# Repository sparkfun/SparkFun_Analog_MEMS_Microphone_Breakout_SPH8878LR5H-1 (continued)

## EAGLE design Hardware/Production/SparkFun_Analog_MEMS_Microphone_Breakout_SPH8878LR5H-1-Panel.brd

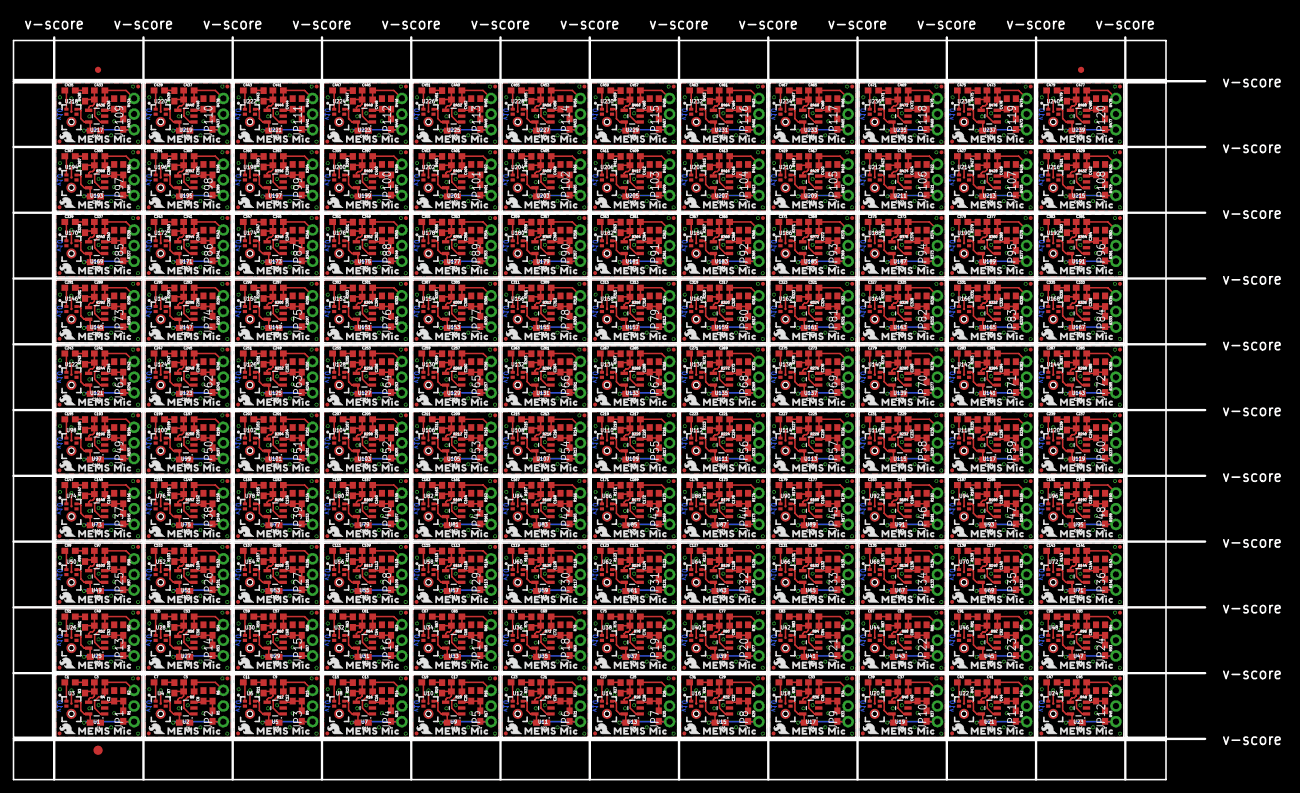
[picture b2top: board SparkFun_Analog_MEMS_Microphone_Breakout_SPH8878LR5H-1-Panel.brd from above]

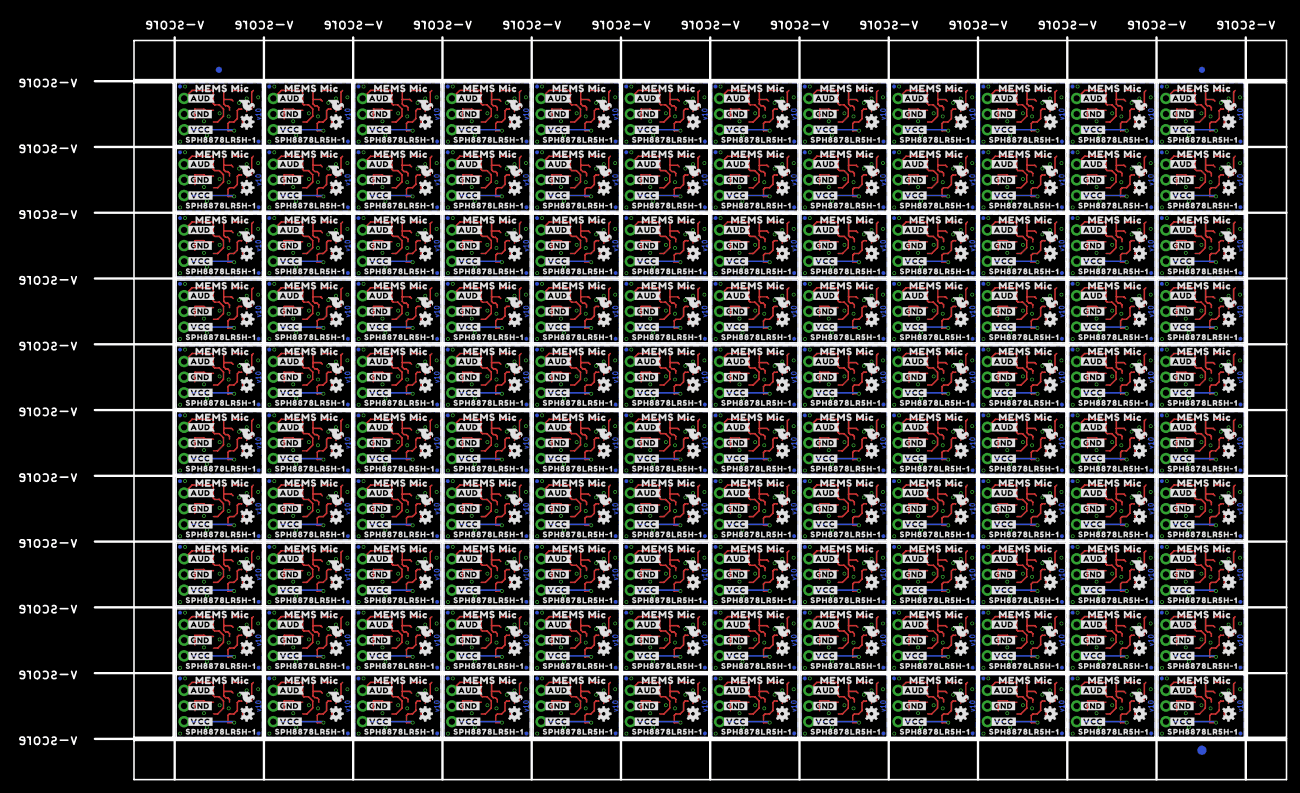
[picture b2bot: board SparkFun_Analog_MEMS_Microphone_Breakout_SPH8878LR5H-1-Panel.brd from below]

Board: 2 copper layers, 193.3 x 120.4 mm, 3006 parts (1203 on the bottom side), 960 nets.

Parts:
C1, C7, C11, C15, C19, C23, C27, C31, C35, C39, C43, C47, C51, C55, C59, C63, C67, C71, C75, C79, C83, C87, C91, C95, C99, C103, C107, C111, C115, C119, C123, C127, C131, C135, C139, C143, C147, C151, C155, C159, C163, C167, C171, C175, C179, C183, C187, C191, C195, C199, C203, C207, C211, C215, C219, C223, C227, C231, C235, C239, C243, C247, C251, C255, C259, C263, C267, C271, C275, C279, C283, C287, C291, C295, C299, C303, C307, C311, C315, C319, C323, C327, C331, C335, C339, C343, C347, C351, C355, C359, C363, C367, C371, C375, C379, C383, C387, C391, C395, C399, C403, C407, C411, C415, C419, C423, C427, C431, C435, C439, C443, C447, C451, C455, C459, C463, C467, C471, C475, C479: 4.7uF; 0603
C2, C8, C12, C16, C20, C24, C28, C32, C36, C40, C44, C48, C52, C56, C60, C64, C68, C72, C76, C80, C84, C88, C92, C96, C100, C104, C108, C112, C116, C120, C124, C128, C132, C136, C140, C144, C148, C152, C156, C160, C164, C168, C172, C176, C180, C184, C188, C192, C196, C200, C204, C208, C212, C216, C220, C224, C228, C232, C236, C240, C244, C248, C252, C256, C260, C264, C268, C272, C276, C280, C284, C288, C292, C296, C300, C304, C308, C312, C316, C320, C324, C328, C332, C336, C340, C344, C348, C352, C356, C360, C364, C368, C372, C376, C380, C384, C388, C392, C396, C400, C404, C408, C412, C416, C420, C424, C428, C432, C436, C440, C444, C448, C452, C456, C460, C464, C468, C472, C476, C480: 1.0uF; 0603
C3, C5, C9, C13, C17, C21, C25, C29, C33, C37, C41, C45, C49, C53, C57, C61, C65, C69, C73, C77, C81, C85, C89, C93, C97, C101, C105, C109, C113, C117, C121, C125, C129, C133, C137, C141, C145, C149, C153, C157, C161, C165, C169, C173, C177, C181, C185, C189, C193, C197, C201, C205, C209, C213, C217, C221, C225, C229, C233, C237, C241, C245, C249, C253, C257, C261, C265, C269, C273, C277, C281, C285, C289, C293, C297, C301, C305, C309, C313, C317, C321, C325, C329, C333, C337, C341, C345, C349, C353, C357, C361, C365, C369, C373, C377, C381, C385, C389, C393, C397, C401, C405, C409, C413, C417, C421, C425, C429, C433, C437, C441, C445, C449, C453, C457, C461, C465, C469, C473, C477: 27pF; 0603
C4, C6, C10, C14, C18, C22, C26, C30, C34, C38, C42, C46, C50, C54, C58, C62, C66, C70, C74, C78, C82, C86, C90, C94, C98, C102, C106, C110, C114, C118, C122, C126, C130, C134, C138, C142, C146, C150, C154, C158, C162, C166, C170, C174, C178, C182, C186, C190, C194, C198, C202, C206, C210, C214, C218, C222, C226, C230, C234, C238, C242, C246, C250, C254, C258, C262, C266, C270, C274, C278, C282, C286, C290, C294, C298, C302, C306, C310, C314, C318, C322, C326, C330, C334, C338, C342, C346, C350, C354, C358, C362, C366, C370, C374, C378, C382, C386, C390, C394, C398, C402, C406, C410, C414, C418, C422, C426, C430, C434, C438, C442, C446, C450, C454, C458, C462, C466, C470, C474, C478: 0.1uF; 0603
E$1, E$2, E$3, E$4: FIDUCIAL-1X2
E$5, E$6: FIDUCIAL-1.5X3
FD1, FD2, FD3, FD4, FD5, FD6, FD7, FD8, FD9, FD10, FD11, FD12, FD13, FD14, FD15, FD16, FD17, FD18, FD19, FD20, FD21, FD22, FD23, FD24, FD25, FD26, FD27, FD28, FD29, FD30, FD31, FD32, FD33, FD34, FD35, FD36, FD37, FD38, FD39, FD40, FD41, FD42, FD43, FD44, FD45, FD46, FD47, FD48, FD49, FD50, FD51, FD52, FD53, FD54, FD55, FD56, FD57, FD58, FD59, FD60, FD61, FD62, FD63, FD64, FD65, FD66, FD67, FD68, FD69, FD70, FD71, FD72, FD73, FD74, FD75, FD76, FD77, FD78, FD79, FD80, FD81, FD82, FD83, FD84, FD85, FD86, FD87, FD88, FD89, FD90, FD91, FD92, FD93, FD94, FD95, FD96, FD97, FD98, FD99, FD100, FD101, FD102, FD103, FD104, FD105, FD106, FD107, FD108, FD109, FD110, FD111, FD112, FD113, FD114, FD115, FD116, FD117, FD118, FD119, FD120, FD121, FD122, FD123, FD124, FD125, FD126, FD127, FD128, FD129, FD130, FD131, FD132, FD133, FD134, FD135, FD136, FD137, FD138, FD139, FD140, FD141, FD142, FD143, FD144, FD145, FD146, FD147, FD148, FD149, FD150, FD151, FD152, FD153, FD154, FD155, FD156, FD157, FD158, FD159, FD160, FD161, FD162, FD163, FD164, FD165, FD166, FD167, FD168, FD169, FD170, FD171, FD172, FD173, FD174, FD175, FD176, FD177, FD178, FD179, FD180, FD181, FD182, FD183, FD184, FD185, FD186, FD187, FD188, FD189, FD190, FD191, FD192, FD193, FD194, FD195, FD196, FD197, FD198, FD199, FD200, FD201, FD202, FD203, FD204, FD205, FD206, FD207, FD208, FD209, FD210, FD211, FD212, FD213, FD214, FD215, FD216, FD217, FD218, FD219, FD220, FD221, FD222, FD223, FD224, FD225, FD226, FD227, FD228, FD229, FD230, FD231, FD232, FD233, FD234, FD235, FD236, FD237, FD238, FD239, FD240, FD241, FD242, FD243, FD244, FD245, FD246, FD247, FD248, FD249, FD250, FD251, FD252, FD253, FD254, FD255, FD256, FD257, FD258, FD259, FD260, FD261, FD262, FD263, FD264, FD265, FD266, FD267, FD268, FD269, FD270, FD271, FD272, FD273, FD274, FD275, FD276, FD277, FD278, FD279, FD280, FD281, FD282, FD283, FD284, FD285, FD286, FD287, FD288, FD289, FD290, FD291, FD292, FD293, FD294, FD295, FD296, FD297, FD298, FD299, FD300, FD301, FD302, FD303, FD304, FD305, FD306, FD307, FD308, FD309, FD310, FD311, FD312, FD313, FD314, FD315, FD316, FD317, FD318, FD319, FD320, FD321, FD322, FD323, FD324, FD325, FD326, FD327, FD328, FD329, FD330, FD331, FD332, FD333, FD334, FD335, FD336, FD337, FD338, FD339, FD340, FD341, FD342, FD343, FD344, FD345, FD346, FD347, FD348, FD349, FD350, FD351, FD352, FD353, FD354, FD355, FD356, FD357, FD358, FD359, FD360, FD361, FD362, FD363, FD364, FD365, FD366, FD367, FD368, FD369, FD370, FD371, FD372, FD373, FD374, FD375, FD376, FD377, FD378, FD379, FD380, FD381, FD382, FD383, FD384, FD385, FD386, FD387, FD388, FD389, FD390, FD391, FD392, FD393, FD394, FD395, FD396, FD397, FD398, FD399, FD400, FD401, FD402, FD403, FD404, FD405, FD406, FD407, FD408, FD409, FD410, FD411, FD412, FD413, FD414, FD415, FD416, FD417, FD418, FD419, FD420, FD421, FD422, FD423, FD424, FD425, FD426, FD427, FD428, FD429, FD430, FD431, FD432, FD433, FD434, FD435, FD436, FD437, FD438, FD439, FD440, FD441, FD442, FD443, FD444, FD445, FD446, FD447, FD448, FD449, FD450, FD451, FD452, FD453, FD454, FD455, FD456, FD457, FD458, FD459, FD460, FD461, FD462, FD463, FD464, FD465, FD466, FD467, FD468, FD469, FD470, FD471, FD472, FD473, FD474, FD475, FD476, FD477, FD478, FD479, FD480: FIDUCIALUFIDUCIAL; FIDUCIAL-MICRO
JP1, JP2, JP3, JP4, JP5, JP6, JP7, JP8, JP9, JP10, JP11, JP12, JP13, JP14, JP15, JP16, JP17, JP18, JP19, JP20, JP21, JP22, JP23, JP24, JP25, JP26, JP27, JP28, JP29, JP30, JP31, JP32, JP33, JP34, JP35, JP36, JP37, JP38, JP39, JP40, JP41, JP42, JP43, JP44, JP45, JP46, JP47, JP48, JP49, JP50, JP51, JP52, JP53, JP54, JP55, JP56, JP57, JP58, JP59, JP60, JP61, JP62, JP63, JP64, JP65, JP66, JP67, JP68, JP69, JP70, JP71, JP72, JP73, JP74, JP75, JP76, JP77, JP78, JP79, JP80, JP81, JP82, JP83, JP84, JP85, JP86, JP87, JP88, JP89, JP90, JP91, JP92, JP93, JP94, JP95, JP96, JP97, JP98, JP99, JP100, JP101, JP102, JP103, JP104, JP105, JP106, JP107, JP108, JP109, JP110, JP111, JP112, JP113, JP114, JP115, JP116, JP117, JP118, JP119, JP120: 1X03_NO_SILK
LOGO1, LOGO3, LOGO4, LOGO6, LOGO7, LOGO9, LOGO10, LOGO12, LOGO13, LOGO15, LOGO16, LOGO18, LOGO19, LOGO21, LOGO22, LOGO24, LOGO25, LOGO27, LOGO28, LOGO30, LOGO31, LOGO33, LOGO34, LOGO36, LOGO37, LOGO39, LOGO40, LOGO42, LOGO43, LOGO45, LOGO46, LOGO48, LOGO49, LOGO51, LOGO52, LOGO54, LOGO55, LOGO57, LOGO58, LOGO60, LOGO61, LOGO63, LOGO64, LOGO66, LOGO67, LOGO69, LOGO70, LOGO72, LOGO73, LOGO75, LOGO76, LOGO78, LOGO79, LOGO81, LOGO82, LOGO84, LOGO85, LOGO87, LOGO88, LOGO90, LOGO91, LOGO93, LOGO94, LOGO96, LOGO97, LOGO99, LOGO100, LOGO102, LOGO103, LOGO105, LOGO106, LOGO108, LOGO109, LOGO111, LOGO112, LOGO114, LOGO115, LOGO117, LOGO118, LOGO120, LOGO121, LOGO123, LOGO124, LOGO126, LOGO127, LOGO129, LOGO130, LOGO132, LOGO133, LOGO135, LOGO136, LOGO138, LOGO139, LOGO141, LOGO142, LOGO144, LOGO145, LOGO147, LOGO148, LOGO150, LOGO151, LOGO153, LOGO154, LOGO156, LOGO157, LOGO159, LOGO160, LOGO162, LOGO163, LOGO165, LOGO166, LOGO168, LOGO169, LOGO171, LOGO172, LOGO174, LOGO175, LOGO177, LOGO178, LOGO180, LOGO181, LOGO183, LOGO184, LOGO186, LOGO187, LOGO189, LOGO190, LOGO192, LOGO193, LOGO195, LOGO196, LOGO198, LOGO199, LOGO201, LOGO202, LOGO204, LOGO205, LOGO207, LOGO208, LOGO210, LOGO211, LOGO213, LOGO214, LOGO216, LOGO217, LOGO219, LOGO220, LOGO222, LOGO223, LOGO225, LOGO226, LOGO228, LOGO229, LOGO231, LOGO232, LOGO234, LOGO235, LOGO237, LOGO238, LOGO240, LOGO241, LOGO243, LOGO244, LOGO246, LOGO247, LOGO249, LOGO250, LOGO252, LOGO253, LOGO255, LOGO256, LOGO258, LOGO259, LOGO261, LOGO262, LOGO264, LOGO265, LOGO267, LOGO268, LOGO270, LOGO271, LOGO273, LOGO274, LOGO276, LOGO277, LOGO279, LOGO280, LOGO282, LOGO283, LOGO285, LOGO286, LOGO288, LOGO289, LOGO291, LOGO292, LOGO294, LOGO295, LOGO297, LOGO298, LOGO300, LOGO301, LOGO303, LOGO304, LOGO306, LOGO307, LOGO309, LOGO310, LOGO312, LOGO313, LOGO315, LOGO316, LOGO318, LOGO319, LOGO321, LOGO322, LOGO324, LOGO325, LOGO327, LOGO328, LOGO330, LOGO331, LOGO333, LOGO334, LOGO336, LOGO337, LOGO339, LOGO340, LOGO342, LOGO343, LOGO345, LOGO346, LOGO348, LOGO349, LOGO351, LOGO352, LOGO354, LOGO355, LOGO357, LOGO358, LOGO360: SFE_LOGO_FLAME.1_INCH; SFE_LOGO_FLAME_.1
LOGO2, LOGO5, LOGO8, LOGO11, LOGO14, LOGO17, LOGO20, LOGO23, LOGO26, LOGO29, LOGO32, LOGO35, LOGO38, LOGO41, LOGO44, LOGO47, LOGO50, LOGO53, LOGO56, LOGO59, LOGO62, LOGO65, LOGO68, LOGO71, LOGO74, LOGO77, LOGO80, LOGO83, LOGO86, LOGO89, LOGO92, LOGO95, LOGO98, LOGO101, LOGO104, LOGO107, LOGO110, LOGO113, LOGO116, LOGO119, LOGO122, LOGO125, LOGO128, LOGO131, LOGO134, LOGO137, LOGO140, LOGO143, LOGO146, LOGO149, LOGO152, LOGO155, LOGO158, LOGO161, LOGO164, LOGO167, LOGO170, LOGO173, LOGO176, LOGO179, LOGO182, LOGO185, LOGO188, LOGO191, LOGO194, LOGO197, LOGO200, LOGO203, LOGO206, LOGO209, LOGO212, LOGO215, LOGO218, LOGO221, LOGO224, LOGO227, LOGO230, LOGO233, LOGO236, LOGO239, LOGO242, LOGO245, LOGO248, LOGO251, LOGO254, LOGO257, LOGO260, LOGO263, LOGO266, LOGO269, LOGO272, LOGO275, LOGO278, LOGO281, LOGO284, LOGO287, LOGO290, LOGO293, LOGO296, LOGO299, LOGO302, LOGO305, LOGO308, LOGO311, LOGO314, LOGO317, LOGO320, LOGO323, LOGO326, LOGO329, LOGO332, LOGO335, LOGO338, LOGO341, LOGO344, LOGO347, LOGO350, LOGO353, LOGO356, LOGO359: OSHW-LOGOMINI; OSHW-LOGO-MINI
OUT-, OUT-1, OUT-2, OUT-3, OUT-4, OUT-5, OUT-6, OUT-7, OUT-8, OUT-9, OUT-10, OUT-11, OUT-12, OUT-13, OUT-14, OUT-15, OUT-16, OUT-17, OUT-18, OUT-19, OUT-20, OUT-21, OUT-22, OUT-23, OUT-24, OUT-25, OUT-26, OUT-27, OUT-28, OUT-29, OUT-30, OUT-31, OUT-32, OUT-33, OUT-34, OUT-35, OUT-36, OUT-37, OUT-38, OUT-39, OUT-40, OUT-41, OUT-42, OUT-43, OUT-44, OUT-45, OUT-46, OUT-47, OUT-48, OUT-49, OUT-50, OUT-51, OUT-52, OUT-53, OUT-54, OUT-55, OUT-56, OUT-57, OUT-58, OUT-59, OUT-60, OUT-61, OUT-62, OUT-63, OUT-64, OUT-65, OUT-66, OUT-67, OUT-68, OUT-69, OUT-70, OUT-71, OUT-72, OUT-73, OUT-74, OUT-75, OUT-76, OUT-77, OUT-78, OUT-79, OUT-80, OUT-81, OUT-82, OUT-83, OUT-84, OUT-85, OUT-86, OUT-87, OUT-88, OUT-89, OUT-90, OUT-91, OUT-92, OUT-93, OUT-94, OUT-95, OUT-96, OUT-97, OUT-98, OUT-99, OUT-100, OUT-101, OUT-102, OUT-103, OUT-104, OUT-105, OUT-106, OUT-107, OUT-108, OUT-109, OUT-110, OUT-111, OUT-112, OUT-113, OUT-114, OUT-115, OUT-116, OUT-117, OUT-118, OUT-119: TP_15TH
R1, R2, R5, R6, R9, R10, R13, R14, R17, R18, R21, R22, R25, R26, R29, R30, R33, R34, R37, R38, R41, R42, R45, R46, R49, R50, R53, R54, R57, R58, R61, R62, R65, R66, R69, R70, R73, R74, R77, R78, R81, R82, R85, R86, R89, R90, R93, R94, R97, R98, R101, R102, R105, R106, R109, R110, R113, R114, R117, R118, R121, R122, R125, R126, R129, R130, R133, R134, R137, R138, R141, R142, R145, R146, R149, R150, R153, R154, R157, R158, R161, R162, R165, R166, R169, R170, R173, R174, R177, R178, R181, R182, R185, R186, R189, R190, R193, R194, R197, R198, R201, R202, R205, R206, R209, R210, R213, R214, R217, R218, R221, R222, R225, R226, R229, R230, R233, R234, R237, R238, R241, R242, R245, R246, R249, R250, R253, R254, R257, R258, R261, R262, R265, R266, R269, R270, R273, R274, R277, R278, R281, R282, R285, R286, R289, R290, R293, R294, R297, R298, R301, R302, R305, R306, R309, R310, R313, R314, R317, R318, R321, R322, R325, R326, R329, R330, R333, R334, R337, R338, R341, R342, R345, R346, R349, R350, R353, R354, R357, R358, R361, R362, R365, R366, R369, R370, R373, R374, R377, R378, R381, R382, R385, R386, R389, R390, R393, R394, R397, R398, R401, R402, R405, R406, R409, R410, R413, R414, R417, R418, R421, R422, R425, R426, R429, R430, R433, R434, R437, R438, R441, R442, R445, R446, R449, R450, R453, R454, R457, R458, R461, R462, R465, R466, R469, R470, R473, R474, R477, R478: 10k; 0603
R3, R7, R11, R15, R19, R23, R27, R31, R35, R39, R43, R47, R51, R55, R59, R63, R67, R71, R75, R79, R83, R87, R91, R95, R99, R103, R107, R111, R115, R119, R123, R127, R131, R135, R139, R143, R147, R151, R155, R159, R163, R167, R171, R175, R179, R183, R187, R191, R195, R199, R203, R207, R211, R215, R219, R223, R227, R231, R235, R239, R243, R247, R251, R255, R259, R263, R267, R271, R275, R279, R283, R287, R291, R295, R299, R303, R307, R311, R315, R319, R323, R327, R331, R335, R339, R343, R347, R351, R355, R359, R363, R367, R371, R375, R379, R383, R387, R391, R395, R399, R403, R407, R411, R415, R419, R423, R427, R431, R435, R439, R443, R447, R451, R455, R459, R463, R467, R471, R475, R479: 4.7k; 0603
R4, R8, R12, R16, R20, R24, R28, R32, R36, R40, R44, R48, R52, R56, R60, R64, R68, R72, R76, R80, R84, R88, R92, R96, R100, R104, R108, R112, R116, R120, R124, R128, R132, R136, R140, R144, R148, R152, R156, R160, R164, R168, R172, R176, R180, R184, R188, R192, R196, R200, R204, R208, R212, R216, R220, R224, R228, R232, R236, R240, R244, R248, R252, R256, R260, R264, R268, R272, R276, R280, R284, R288, R292, R296, R300, R304, R308, R312, R316, R320, R324, R328, R332, R336, R340, R344, R348, R352, R356, R360, R364, R368, R372, R376, R380, R384, R388, R392, R396, R400, R404, R408, R412, R416, R420, R424, R428, R432, R436, R440, R444, R448, R452, R456, R460, R464, R468, R472, R476, R480: 300k; 0603
U1, U2, U5, U7, U9, U11, U13, U15, U17, U19, U21, U23, U25, U27, U29, U31, U33, U35, U37, U39, U41, U43, U45, U47, U49, U51, U53, U55, U57, U59, U61, U63, U65, U67, U69, U71, U73, U75, U77, U79, U81, U83, U85, U87, U89, U91, U93, U95, U97, U99, U101, U103, U105, U107, U109, U111, U113, U115, U117, U119, U121, U123, U125, U127, U129, U131, U133, U135, U137, U139, U141, U143, U145, U147, U149, U151, U153, U155, U157, U159, U161, U163, U165, U167, U169, U171, U173, U175, U177, U179, U181, U183, U185, U187, U189, U191, U193, U195, U197, U199, U201, U203, U205, U207, U209, U211, U213, U215, U217, U219, U221, U223, U225, U227, U229, U231, U233, U235, U237, U239: OPA344; SOT23-5
U3, U4, U6, U8, U10, U12, U14, U16, U18, U20, U22, U24, U26, U28, U30, U32, U34, U36, U38, U40, U42, U44, U46, U48, U50, U52, U54, U56, U58, U60, U62, U64, U66, U68, U70, U72, U74, U76, U78, U80, U82, U84, U86, U88, U90, U92, U94, U96, U98, U100, U102, U104, U106, U108, U110, U112, U114, U116, U118, U120, U122, U124, U126, U128, U130, U132, U134, U136, U138, U140, U142, U144, U146, U148, U150, U152, U154, U156, U158, U160, U162, U164, U166, U168, U170, U172, U174, U176, U178, U180, U182, U184, U186, U188, U190, U192, U194, U196, U198, U200, U202, U204, U206, U208, U210, U212, U214, U216, U218, U220, U222, U224, U226, U228, U230, U232, U234, U236, U238, U240: SPH8878LR5H-1
U$1, U$2, U$7, U$11, U$13, U$17, U$19, U$23, U$25, U$29, U$31, U$35, U$37, U$41, U$43, U$47, U$49, U$53, U$55, U$59, U$61, U$65, U$67, U$71, U$73, U$77, U$79, U$83, U$85, U$89, U$91, U$95, U$97, U$101, U$103, U$107, U$109, U$113, U$115, U$119, U$121, U$125, U$127, U$131, U$133, U$137, U$139, U$143, U$145, U$149, U$151, U$155, U$157, U$161, U$163, U$167, U$169, U$173, U$175, U$179, U$181, U$185, U$187, U$191, U$193, U$197, U$199, U$203, U$205, U$209, U$211, U$215, U$217, U$221, U$223, U$227, U$229, U$233, U$235, U$239, U$241, U$245, U$247, U$251, U$253, U$257, U$259, U$263, U$265, U$269, U$271, U$275, U$277, U$281, U$283, U$287, U$289, U$293, U$295, U$299, U$301, U$305, U$307, U$311, U$313, U$317, U$319, U$323, U$325, U$329, U$331, U$335, U$337, U$341, U$343, U$347, U$349, U$353, U$355, U$359, U$361, U$365, U$367, U$371, U$373, U$377, U$379, U$383, U$385, U$389, U$391, U$395, U$397, U$401, U$403, U$407, U$409, U$413, U$415, U$419, U$421, U$425, U$427, U$431, U$433, U$437, U$439, U$443, U$445, U$449, U$451, U$455, U$457, U$461, U$463, U$467, U$469, U$473, U$475, U$479, U$481, U$485, U$487, U$491, U$493, U$497, U$499, U$503, U$505, U$509, U$511, U$515, U$517, U$521, U$523, U$527, U$529, U$533, U$535, U$539, U$541, U$545, U$547, U$551, U$553, U$557, U$559, U$563, U$565, U$569, U$571, U$575, U$577, U$581, U$583, U$587, U$589, U$593, U$595, U$599, U$601, U$605, U$607, U$611, U$613, U$617, U$619, U$623, U$625, U$629, U$631, U$635, U$637, U$641, U$643, U$647, U$649, U$653, U$655, U$659, U$661, U$665, U$667, U$671, U$673, U$677, U$679, U$683, U$685, U$689, U$691, U$695, U$697, U$701, U$703, U$707, U$709, U$713, U$715, U$719: MEMS_MIC0
U$3, U$6, U$14, U$20, U$26, U$32, U$38, U$44, U$50, U$56, U$62, U$68, U$74, U$80, U$86, U$92, U$98, U$104, U$110, U$116, U$122, U$128, U$134, U$140, U$146, U$152, U$158, U$164, U$170, U$176, U$182, U$188, U$194, U$200, U$206, U$212, U$218, U$224, U$230, U$236, U$242, U$248, U$254, U$260, U$266, U$272, U$278, U$284, U$290, U$296, U$302, U$308, U$314, U$320, U$326, U$332, U$338, U$344, U$350, U$356, U$362, U$368, U$374, U$380, U$386, U$392, U$398, U$404, U$410, U$416, U$422, U$428, U$434, U$440, U$446, U$452, U$458, U$464, U$470, U$476, U$482, U$488, U$494, U$500, U$506, U$512, U$518, U$524, U$530, U$536, U$542, U$548, U$554, U$560, U$566, U$572, U$578, U$584, U$590, U$596, U$602, U$608, U$614, U$620, U$626, U$632, U$638, U$644, U$650, U$656, U$662, U$668, U$674, U$680, U$686, U$692, U$698, U$704, U$710, U$716: #GND#0
U$4, U$8, U$15, U$21, U$27, U$33, U$39, U$45, U$51, U$57, U$63, U$69, U$75, U$81, U$87, U$93, U$99, U$105, U$111, U$117, U$123, U$129, U$135, U$141, U$147, U$153, U$159, U$165, U$171, U$177, U$183, U$189, U$195, U$201, U$207, U$213, U$219, U$225, U$231, U$237, U$243, U$249, U$255, U$261, U$267, U$273, U$279, U$285, U$291, U$297, U$303, U$309, U$315, U$321, U$327, U$333, U$339, U$345, U$351, U$357, U$363, U$369, U$375, U$381, U$387, U$393, U$399, U$405, U$411, U$417, U$423, U$429, U$435, U$441, U$447, U$453, U$459, U$465, U$471, U$477, U$483, U$489, U$495, U$501, U$507, U$513, U$519, U$525, U$531, U$537, U$543, U$549, U$555, U$561, U$567, U$573, U$579, U$585, U$591, U$597, U$603, U$609, U$615, U$621, U$627, U$633, U$639, U$645, U$651, U$657, U$663, U$669, U$675, U$681, U$687, U$693, U$699, U$705, U$711, U$717: #VCC#0
U$5, U$10, U$16, U$22, U$28, U$34, U$40, U$46, U$52, U$58, U$64, U$70, U$76, U$82, U$88, U$94, U$100, U$106, U$112, U$118, U$124, U$130, U$136, U$142, U$148, U$154, U$160, U$166, U$172, U$178, U$184, U$190, U$196, U$202, U$208, U$214, U$220, U$226, U$232, U$238, U$244, U$250, U$256, U$262, U$268, U$274, U$280, U$286, U$292, U$298, U$304, U$310, U$316, U$322, U$328, U$334, U$340, U$346, U$352, U$358, U$364, U$370, U$376, U$382, U$388, U$394, U$400, U$406, U$412, U$418, U$424, U$430, U$436, U$442, U$448, U$454, U$460, U$466, U$472, U$478, U$484, U$490, U$496, U$502, U$508, U$514, U$520, U$526, U$532, U$538, U$544, U$550, U$556, U$562, U$568, U$574, U$580, U$586, U$592, U$598, U$604, U$610, U$616, U$622, U$628, U$634, U$640, U$646, U$652, U$658, U$664, U$670, U$676, U$682, U$688, U$694, U$700, U$706, U$712, U$718: #AUD#0
U$9, U$12, U$18, U$24, U$30, U$36, U$42, U$48, U$54, U$60, U$66, U$72, U$78, U$84, U$90, U$96, U$102, U$108, U$114, U$120, U$126, U$132, U$138, U$144, U$150, U$156, U$162, U$168, U$174, U$180, U$186, U$192, U$198, U$204, U$210, U$216, U$222, U$228, U$234, U$240, U$246, U$252, U$258, U$264, U$270, U$276, U$282, U$288, U$294, U$300, U$306, U$312, U$318, U$324, U$330, U$336, U$342, U$348, U$354, U$360, U$366, U$372, U$378, U$384, U$390, U$396, U$402, U$408, U$414, U$420, U$426, U$432, U$438, U$444, U$450, U$456, U$462, U$468, U$474, U$480, U$486, U$492, U$498, U$504, U$510, U$516, U$522, U$528, U$534, U$540, U$546, U$552, U$558, U$564, U$570, U$576, U$582, U$588, U$594, U$600, U$606, U$612, U$618, U$624, U$630, U$636, U$642, U$648, U$654, U$660, U$666, U$672, U$678, U$684, U$690, U$696, U$702, U$708, U$714, U$720: SPH8878LR5H#10

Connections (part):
AUD: C3.2, JP1.3, R4.1, U1.1
AUD1: C5.2, JP2.3, R8.1, U2.1
AUD2: C9.2, JP3.3, R12.1, U5.1
AUD3: C13.2, JP4.3, R16.1, U7.1
AUD4: C17.2, JP5.3, R20.1, U9.1
AUD5: C21.2, JP6.3, R24.1, U11.1
AUD6: C25.2, JP7.3, R28.1, U13.1
AUD7: C29.2, JP8.3, R32.1, U15.1
AUD8: C33.2, JP9.3, R36.1, U17.1
AUD9: C37.2, JP10.3, R40.1, U19.1
AUD10: C41.2, JP11.3, R44.1, U21.1
AUD11: C45.2, JP12.3, R48.1, U23.1
AUD12: C49.2, JP13.3, R52.1, U25.1
AUD13: C53.2, JP14.3, R56.1, U27.1
AUD14: C57.2, JP15.3, R60.1, U29.1
AUD15: C61.2, JP16.3, R64.1, U31.1
AUD16: C65.2, JP17.3, R68.1, U33.1
AUD17: C69.2, JP18.3, R72.1, U35.1
AUD18: C73.2, JP19.3, R76.1, U37.1
AUD19: C77.2, JP20.3, R80.1, U39.1
AUD20: C81.2, JP21.3, R84.1, U41.1
AUD21: C85.2, JP22.3, R88.1, U43.1
AUD22: C89.2, JP23.3, R92.1, U45.1
AUD23: C93.2, JP24.3, R96.1, U47.1
AUD24: C97.2, JP25.3, R100.1, U49.1
AUD25: C101.2, JP26.3, R104.1, U51.1
AUD26: C105.2, JP27.3, R108.1, U53.1
AUD27: C109.2, JP28.3, R112.1, U55.1
AUD28: C113.2, JP29.3, R116.1, U57.1
AUD29: C117.2, JP30.3, R120.1, U59.1
AUD30: C121.2, JP31.3, R124.1, U61.1
AUD31: C125.2, JP32.3, R128.1, U63.1
AUD32: C129.2, JP33.3, R132.1, U65.1
AUD33: C133.2, JP34.3, R136.1, U67.1
AUD34: C137.2, JP35.3, R140.1, U69.1
AUD35: C141.2, JP36.3, R144.1, U71.1
AUD36: C145.2, JP37.3, R148.1, U73.1
AUD37: C149.2, JP38.3, R152.1, U75.1
AUD38: C153.2, JP39.3, R156.1, U77.1
AUD39: C157.2, JP40.3, R160.1, U79.1
AUD40: C161.2, JP41.3, R164.1, U81.1
AUD41: C165.2, JP42.3, R168.1, U83.1
AUD42: C169.2, JP43.3, R172.1, U85.1
AUD43: C173.2, JP44.3, R176.1, U87.1
AUD44: C177.2, JP45.3, R180.1, U89.1
AUD45: C181.2, JP46.3, R184.1, U91.1
AUD46: C185.2, JP47.3, R188.1, U93.1
AUD47: C189.2, JP48.3, R192.1, U95.1
AUD48: C193.2, JP49.3, R196.1, U97.1
AUD49: C197.2, JP50.3, R200.1, U99.1
AUD50: C201.2, JP51.3, R204.1, U101.1
AUD51: C205.2, JP52.3, R208.1, U103.1
AUD52: C209.2, JP53.3, R212.1, U105.1
AUD53: C213.2, JP54.3, R216.1, U107.1
AUD54: C217.2, JP55.3, R220.1, U109.1
AUD55: C221.2, JP56.3, R224.1, U111.1
AUD56: C225.2, JP57.3, R228.1, U113.1
AUD57: C229.2, JP58.3, R232.1, U115.1
AUD58: C233.2, JP59.3, R236.1, U117.1
AUD59: C237.2, JP60.3, R240.1, U119.1
AUD60: C241.2, JP61.3, R244.1, U121.1
AUD61: C245.2, JP62.3, R248.1, U123.1
AUD62: C249.2, JP63.3, R252.1, U125.1
AUD63: C253.2, JP64.3, R256.1, U127.1
AUD64: C257.2, JP65.3, R260.1, U129.1
AUD65: C261.2, JP66.3, R264.1, U131.1
AUD66: C265.2, JP67.3, R268.1, U133.1
AUD67: C269.2, JP68.3, R272.1, U135.1
AUD68: C273.2, JP69.3, R276.1, U137.1
AUD69: C277.2, JP70.3, R280.1, U139.1
AUD70: C281.2, JP71.3, R284.1, U141.1
AUD71: C285.2, JP72.3, R288.1, U143.1
AUD72: C289.2, JP73.3, R292.1, U145.1
AUD73: C293.2, JP74.3, R296.1, U147.1
AUD74: C297.2, JP75.3, R300.1, U149.1
AUD75: C301.2, JP76.3, R304.1, U151.1
AUD76: C305.2, JP77.3, R308.1, U153.1
AUD77: C309.2, JP78.3, R312.1, U155.1
AUD78: C313.2, JP79.3, R316.1, U157.1
AUD79: C317.2, JP80.3, R320.1, U159.1
AUD80: C321.2, JP81.3, R324.1, U161.1
AUD81: C325.2, JP82.3, R328.1, U163.1
AUD82: C329.2, JP83.3, R332.1, U165.1
AUD83: C333.2, JP84.3, R336.1, U167.1
AUD84: C337.2, JP85.3, R340.1, U169.1
AUD85: C341.2, JP86.3, R344.1, U171.1
AUD86: C345.2, JP87.3, R348.1, U173.1
AUD87: C349.2, JP88.3, R352.1, U175.1
AUD88: C353.2, JP89.3, R356.1, U177.1
AUD89: C357.2, JP90.3, R360.1, U179.1
AUD90: C361.2, JP91.3, R364.1, U181.1
AUD91: C365.2, JP92.3, R368.1, U183.1
AUD92: C369.2, JP93.3, R372.1, U185.1
AUD93: C373.2, JP94.3, R376.1, U187.1
AUD94: C377.2, JP95.3, R380.1, U189.1
AUD95: C381.2, JP96.3, R384.1, U191.1
AUD96: C385.2, JP97.3, R388.1, U193.1
AUD97: C389.2, JP98.3, R392.1, U195.1
AUD98: C393.2, JP99.3, R396.1, U197.1
AUD99: C397.2, JP100.3, R400.1, U199.1
AUD100: C401.2, JP101.3, R404.1, U201.1
AUD101: C405.2, JP102.3, R408.1, U203.1
AUD102: C409.2, JP103.3, R412.1, U205.1
AUD103: C413.2, JP104.3, R416.1, U207.1
AUD104: C417.2, JP105.3, R420.1, U209.1
AUD105: C421.2, JP106.3, R424.1, U211.1
AUD106: C425.2, JP107.3, R428.1, U213.1
AUD107: C429.2, JP108.3, R432.1, U215.1
AUD108: C433.2, JP109.3, R436.1, U217.1
AUD109: C437.2, JP110.3, R440.1, U219.1
AUD110: C441.2, JP111.3, R444.1, U221.1
AUD111: C445.2, JP112.3, R448.1, U223.1
AUD112: C449.2, JP113.3, R452.1, U225.1
AUD113: C453.2, JP114.3, R456.1, U227.1
AUD114: C457.2, JP115.3, R460.1, U229.1
AUD115: C461.2, JP116.3, R464.1, U231.1
AUD116: C465.2, JP117.3, R468.1, U233.1
AUD117: C469.2, JP118.3, R472.1, U235.1
AUD118: C473.2, JP119.3, R476.1, U237.1
AUD119: C477.2, JP120.3, R480.1, U239.1
GND: C2.2, C4.1, JP1.2, R2.1, U1.2, U3.2, U3.3, U3.4
GND1: C6.1, C8.2, JP2.2, R6.1, U2.2, U4.2, U4.3, U4.4
GND2: C10.1, C12.2, JP3.2, R10.1, U5.2, U6.2, U6.3, U6.4
GND3: C14.1, C16.2, JP4.2, R14.1, U7.2, U8.2, U8.3, U8.4
GND4: C18.1, C20.2, JP5.2, R18.1, U9.2, U10.2, U10.3, U10.4
GND5: C22.1, C24.2, JP6.2, R22.1, U11.2, U12.2, U12.3, U12.4
GND6: C26.1, C28.2, JP7.2, R26.1, U13.2, U14.2, U14.3, U14.4
GND7: C30.1, C32.2, JP8.2, R30.1, U15.2, U16.2, U16.3, U16.4
GND8: C34.1, C36.2, JP9.2, R34.1, U17.2, U18.2, U18.3, U18.4
GND9: C38.1, C40.2, JP10.2, R38.1, U19.2, U20.2, U20.3, U20.4
GND10: C42.1, C44.2, JP11.2, R42.1, U21.2, U22.2, U22.3, U22.4
GND11: C46.1, C48.2, JP12.2, R46.1, U23.2, U24.2, U24.3, U24.4
GND12: C50.1, C52.2, JP13.2, R50.1, U25.2, U26.2, U26.3, U26.4
GND13: C54.1, C56.2, JP14.2, R54.1, U27.2, U28.2, U28.3, U28.4
GND14: C58.1, C60.2, JP15.2, R58.1, U29.2, U30.2, U30.3, U30.4
GND15: C62.1, C64.2, JP16.2, R62.1, U31.2, U32.2, U32.3, U32.4
GND16: C66.1, C68.2, JP17.2, R66.1, U33.2, U34.2, U34.3, U34.4
GND17: C70.1, C72.2, JP18.2, R70.1, U35.2, U36.2, U36.3, U36.4
GND18: C74.1, C76.2, JP19.2, R74.1, U37.2, U38.2, U38.3, U38.4
GND19: C78.1, C80.2, JP20.2, R78.1, U39.2, U40.2, U40.3, U40.4
GND20: C82.1, C84.2, JP21.2, R82.1, U41.2, U42.2, U42.3, U42.4
GND21: C86.1, C88.2, JP22.2, R86.1, U43.2, U44.2, U44.3, U44.4
GND22: C90.1, C92.2, JP23.2, R90.1, U45.2, U46.2, U46.3, U46.4
GND23: C94.1, C96.2, JP24.2, R94.1, U47.2, U48.2, U48.3, U48.4
GND24: C98.1, C100.2, JP25.2, R98.1, U49.2, U50.2, U50.3, U50.4
GND25: C102.1, C104.2, JP26.2, R102.1, U51.2, U52.2, U52.3, U52.4
GND26: C106.1, C108.2, JP27.2, R106.1, U53.2, U54.2, U54.3, U54.4
GND27: C110.1, C112.2, JP28.2, R110.1, U55.2, U56.2, U56.3, U56.4
GND28: C114.1, C116.2, JP29.2, R114.1, U57.2, U58.2, U58.3, U58.4
GND29: C118.1, C120.2, JP30.2, R118.1, U59.2, U60.2, U60.3, U60.4
GND30: C122.1, C124.2, JP31.2, R122.1, U61.2, U62.2, U62.3, U62.4
GND31: C126.1, C128.2, JP32.2, R126.1, U63.2, U64.2, U64.3, U64.4
GND32: C130.1, C132.2, JP33.2, R130.1, U65.2, U66.2, U66.3, U66.4
GND33: C134.1, C136.2, JP34.2, R134.1, U67.2, U68.2, U68.3, U68.4
GND34: C138.1, C140.2, JP35.2, R138.1, U69.2, U70.2, U70.3, U70.4
GND35: C142.1, C144.2, JP36.2, R142.1, U71.2, U72.2, U72.3, U72.4
GND36: C146.1, C148.2, JP37.2, R146.1, U73.2, U74.2, U74.3, U74.4
GND37: C150.1, C152.2, JP38.2, R150.1, U75.2, U76.2, U76.3, U76.4
GND38: C154.1, C156.2, JP39.2, R154.1, U77.2, U78.2, U78.3, U78.4
GND39: C158.1, C160.2, JP40.2, R158.1, U79.2, U80.2, U80.3, U80.4
GND40: C162.1, C164.2, JP41.2, R162.1, U81.2, U82.2, U82.3, U82.4
GND41: C166.1, C168.2, JP42.2, R166.1, U83.2, U84.2, U84.3, U84.4
GND42: C170.1, C172.2, JP43.2, R170.1, U85.2, U86.2, U86.3, U86.4
GND43: C174.1, C176.2, JP44.2, R174.1, U87.2, U88.2, U88.3, U88.4
GND44: C178.1, C180.2, JP45.2, R178.1, U89.2, U90.2, U90.3, U90.4
GND45: C182.1, C184.2, JP46.2, R182.1, U91.2, U92.2, U92.3, U92.4
GND46: C186.1, C188.2, JP47.2, R186.1, U93.2, U94.2, U94.3, U94.4
GND47: C190.1, C192.2, JP48.2, R190.1, U95.2, U96.2, U96.3, U96.4
GND48: C194.1, C196.2, JP49.2, R194.1, U97.2, U98.2, U98.3, U98.4
GND49: C198.1, C200.2, JP50.2, R198.1, U99.2, U100.2, U100.3, U100.4
GND50: C202.1, C204.2, JP51.2, R202.1, U101.2, U102.2, U102.3, U102.4
GND51: C206.1, C208.2, JP52.2, R206.1, U103.2, U104.2, U104.3, U104.4
GND52: C210.1, C212.2, JP53.2, R210.1, U105.2, U106.2, U106.3, U106.4
GND53: C214.1, C216.2, JP54.2, R214.1, U107.2, U108.2, U108.3, U108.4
GND54: C218.1, C220.2, JP55.2, R218.1, U109.2, U110.2, U110.3, U110.4
GND55: C222.1, C224.2, JP56.2, R222.1, U111.2, U112.2, U112.3, U112.4
GND56: C226.1, C228.2, JP57.2, R226.1, U113.2, U114.2, U114.3, U114.4
GND57: C230.1, C232.2, JP58.2, R230.1, U115.2, U116.2, U116.3, U116.4
GND58: C234.1, C236.2, JP59.2, R234.1, U117.2, U118.2, U118.3, U118.4
GND59: C238.1, C240.2, JP60.2, R238.1, U119.2, U120.2, U120.3, U120.4
GND60: C242.1, C244.2, JP61.2, R242.1, U121.2, U122.2, U122.3, U122.4
GND61: C246.1, C248.2, JP62.2, R246.1, U123.2, U124.2, U124.3, U124.4
GND62: C250.1, C252.2, JP63.2, R250.1, U125.2, U126.2, U126.3, U126.4
GND63: C254.1, C256.2, JP64.2, R254.1, U127.2, U128.2, U128.3, U128.4
GND64: C258.1, C260.2, JP65.2, R258.1, U129.2, U130.2, U130.3, U130.4
GND65: C262.1, C264.2, JP66.2, R262.1, U131.2, U132.2, U132.3, U132.4
GND66: C266.1, C268.2, JP67.2, R266.1, U133.2, U134.2, U134.3, U134.4
GND67: C270.1, C272.2, JP68.2, R270.1, U135.2, U136.2, U136.3, U136.4
GND68: C274.1, C276.2, JP69.2, R274.1, U137.2, U138.2, U138.3, U138.4
GND69: C278.1, C280.2, JP70.2, R278.1, U139.2, U140.2, U140.3, U140.4
GND70: C282.1, C284.2, JP71.2, R282.1, U141.2, U142.2, U142.3, U142.4
GND71: C286.1, C288.2, JP72.2, R286.1, U143.2, U144.2, U144.3, U144.4
GND72: C290.1, C292.2, JP73.2, R290.1, U145.2, U146.2, U146.3, U146.4
GND73: C294.1, C296.2, JP74.2, R294.1, U147.2, U148.2, U148.3, U148.4
GND74: C298.1, C300.2, JP75.2, R298.1, U149.2, U150.2, U150.3, U150.4
GND75: C302.1, C304.2, JP76.2, R302.1, U151.2, U152.2, U152.3, U152.4
GND76: C306.1, C308.2, JP77.2, R306.1, U153.2, U154.2, U154.3, U154.4
GND77: C310.1, C312.2, JP78.2, R310.1, U155.2, U156.2, U156.3, U156.4
GND78: C314.1, C316.2, JP79.2, R314.1, U157.2, U158.2, U158.3, U158.4
GND79: C318.1, C320.2, JP80.2, R318.1, U159.2, U160.2, U160.3, U160.4
GND80: C322.1, C324.2, JP81.2, R322.1, U161.2, U162.2, U162.3, U162.4
GND81: C326.1, C328.2, JP82.2, R326.1, U163.2, U164.2, U164.3, U164.4
GND82: C330.1, C332.2, JP83.2, R330.1, U165.2, U166.2, U166.3, U166.4
GND83: C334.1, C336.2, JP84.2, R334.1, U167.2, U168.2, U168.3, U168.4
GND84: C338.1, C340.2, JP85.2, R338.1, U169.2, U170.2, U170.3, U170.4
GND85: C342.1, C344.2, JP86.2, R342.1, U171.2, U172.2, U172.3, U172.4
GND86: C346.1, C348.2, JP87.2, R346.1, U173.2, U174.2, U174.3, U174.4
GND87: C350.1, C352.2, JP88.2, R350.1, U175.2, U176.2, U176.3, U176.4
GND88: C354.1, C356.2, JP89.2, R354.1, U177.2, U178.2, U178.3, U178.4
GND89: C358.1, C360.2, JP90.2, R358.1, U179.2, U180.2, U180.3, U180.4
GND90: C362.1, C364.2, JP91.2, R362.1, U181.2, U182.2, U182.3, U182.4
GND91: C366.1, C368.2, JP92.2, R366.1, U183.2, U184.2, U184.3, U184.4
GND92: C370.1, C372.2, JP93.2, R370.1, U185.2, U186.2, U186.3, U186.4
GND93: C374.1, C376.2, JP94.2, R374.1, U187.2, U188.2, U188.3, U188.4
GND94: C378.1, C380.2, JP95.2, R378.1, U189.2, U190.2, U190.3, U190.4
GND95: C382.1, C384.2, JP96.2, R382.1, U191.2, U192.2, U192.3, U192.4
GND96: C386.1, C388.2, JP97.2, R386.1, U193.2, U194.2, U194.3, U194.4
GND97: C390.1, C392.2, JP98.2, R390.1, U195.2, U196.2, U196.3, U196.4
GND98: C394.1, C396.2, JP99.2, R394.1, U197.2, U198.2, U198.3, U198.4
GND99: C398.1, C400.2, JP100.2, R398.1, U199.2, U200.2, U200.3, U200.4
GND100: C402.1, C404.2, JP101.2, R402.1, U201.2, U202.2, U202.3, U202.4
GND101: C406.1, C408.2, JP102.2, R406.1, U203.2, U204.2, U204.3, U204.4
GND102: C410.1, C412.2, JP103.2, R410.1, U205.2, U206.2, U206.3, U206.4
GND103: C414.1, C416.2, JP104.2, R414.1, U207.2, U208.2, U208.3, U208.4
GND104: C418.1, C420.2, JP105.2, R418.1, U209.2, U210.2, U210.3, U210.4
GND105: C422.1, C424.2, JP106.2, R422.1, U211.2, U212.2, U212.3, U212.4
GND106: C426.1, C428.2, JP107.2, R426.1, U213.2, U214.2, U214.3, U214.4
GND107: C430.1, C432.2, JP108.2, R430.1, U215.2, U216.2, U216.3, U216.4
GND108: C434.1, C436.2, JP109.2, R434.1, U217.2, U218.2, U218.3, U218.4
GND109: C438.1, C440.2, JP110.2, R438.1, U219.2, U220.2, U220.3, U220.4
GND110: C442.1, C444.2, JP111.2, R442.1, U221.2, U222.2, U222.3, U222.4
GND111: C446.1, C448.2, JP112.2, R446.1, U223.2, U224.2, U224.3, U224.4
GND112: C450.1, C452.2, JP113.2, R450.1, U225.2, U226.2, U226.3, U226.4
GND113: C454.1, C456.2, JP114.2, R454.1, U227.2, U228.2, U228.3, U228.4
GND114: C458.1, C460.2, JP115.2, R458.1, U229.2, U230.2, U230.3, U230.4
GND115: C462.1, C464.2, JP116.2, R462.1, U231.2, U232.2, U232.3, U232.4
GND116: C466.1, C468.2, JP117.2, R466.1, U233.2, U234.2, U234.3, U234.4
GND117: C470.1, C472.2, JP118.2, R470.1, U235.2, U236.2, U236.3, U236.4
GND118: C474.1, C476.2, JP119.2, R474.1, U237.2, U238.2, U238.3, U238.4
GND119: C478.1, C480.2, JP120.2, R478.1, U239.2, U240.2, U240.3, U240.4
unnamed: C1.1, U3.1
unnamed: C3.1, R3.1, R4.2, U1.4
unnamed: OUT-.1, U3.6
unnamed: C7.1, U4.1
unnamed: C5.1, R7.1, R8.2, U2.4
unnamed: C1.2, R3.2
unnamed: C2.1, R1.1, R2.2, U1.3
unnamed: C7.2, R7.2
unnamed: C8.1, R5.1, R6.2, U2.3
unnamed: OUT-1.1, U4.6
unnamed: C11.1, U6.1
unnamed: C9.1, R11.1, R12.2, U5.4
unnamed: C11.2, R11.2
unnamed: C12.1, R9.1, R10.2, U5.3
unnamed: OUT-2.1, U6.6
unnamed: C15.1, U8.1
unnamed: C13.1, R15.1, R16.2, U7.4
unnamed: C15.2, R15.2
unnamed: C16.1, R13.1, R14.2, U7.3
unnamed: OUT-3.1, U8.6
unnamed: C19.1, U10.1
unnamed: C17.1, R19.1, R20.2, U9.4
unnamed: C19.2, R19.2
unnamed: C20.1, R17.1, R18.2, U9.3
unnamed: OUT-4.1, U10.6
unnamed: C23.1, U12.1
unnamed: C21.1, R23.1, R24.2, U11.4
unnamed: C23.2, R23.2
unnamed: C24.1, R21.1, R22.2, U11.3
unnamed: OUT-5.1, U12.6
unnamed: C27.1, U14.1
unnamed: C25.1, R27.1, R28.2, U13.4
unnamed: C27.2, R27.2
unnamed: C28.1, R25.1, R26.2, U13.3
unnamed: OUT-6.1, U14.6
unnamed: C31.1, U16.1
unnamed: C29.1, R31.1, R32.2, U15.4
unnamed: C31.2, R31.2
unnamed: C32.1, R29.1, R30.2, U15.3
unnamed: OUT-7.1, U16.6
unnamed: C35.1, U18.1
unnamed: C33.1, R35.1, R36.2, U17.4
unnamed: C35.2, R35.2
unnamed: C36.1, R33.1, R34.2, U17.3
unnamed: OUT-8.1, U18.6
unnamed: C39.1, U20.1
unnamed: C37.1, R39.1, R40.2, U19.4
unnamed: C39.2, R39.2
unnamed: C40.1, R37.1, R38.2, U19.3
unnamed: OUT-9.1, U20.6
unnamed: C43.1, U22.1
unnamed: C41.1, R43.1, R44.2, U21.4
unnamed: C43.2, R43.2
unnamed: C44.1, R41.1, R42.2, U21.3
unnamed: OUT-10.1, U22.6
unnamed: C47.1, U24.1
unnamed: C45.1, R47.1, R48.2, U23.4
unnamed: C47.2, R47.2
unnamed: C48.1, R45.1, R46.2, U23.3
unnamed: OUT-11.1, U24.6
unnamed: C51.1, U26.1
unnamed: C49.1, R51.1, R52.2, U25.4
unnamed: C51.2, R51.2
unnamed: C52.1, R49.1, R50.2, U25.3
unnamed: OUT-12.1, U26.6
unnamed: C55.1, U28.1
unnamed: C53.1, R55.1, R56.2, U27.4
unnamed: C55.2, R55.2
unnamed: C56.1, R53.1, R54.2, U27.3
unnamed: OUT-13.1, U28.6
unnamed: C59.1, U30.1
unnamed: C57.1, R59.1, R60.2, U29.4
unnamed: C59.2, R59.2
unnamed: C60.1, R57.1, R58.2, U29.3
unnamed: OUT-14.1, U30.6
unnamed: C63.1, U32.1
unnamed: C61.1, R63.1, R64.2, U31.4
unnamed: C63.2, R63.2
unnamed: C64.1, R61.1, R62.2, U31.3
unnamed: OUT-15.1, U32.6
unnamed: C67.1, U34.1
unnamed: C65.1, R67.1, R68.2, U33.4
unnamed: C67.2, R67.2
unnamed: C68.1, R65.1, R66.2, U33.3
unnamed: OUT-16.1, U34.6
unnamed: C71.1, U36.1
unnamed: C69.1, R71.1, R72.2, U35.4
unnamed: C71.2, R71.2
unnamed: C72.1, R69.1, R70.2, U35.3
unnamed: OUT-17.1, U36.6
unnamed: C75.1, U38.1
unnamed: C73.1, R75.1, R76.2, U37.4
unnamed: C75.2, R75.2
unnamed: C76.1, R73.1, R74.2, U37.3
unnamed: OUT-18.1, U38.6
unnamed: C79.1, U40.1
unnamed: C77.1, R79.1, R80.2, U39.4
unnamed: C79.2, R79.2
unnamed: C80.1, R77.1, R78.2, U39.3
unnamed: OUT-19.1, U40.6
unnamed: C83.1, U42.1
unnamed: C81.1, R83.1, R84.2, U41.4
unnamed: C83.2, R83.2
unnamed: C84.1, R81.1, R82.2, U41.3
unnamed: OUT-20.1, U42.6
unnamed: C87.1, U44.1
unnamed: C85.1, R87.1, R88.2, U43.4
unnamed: C87.2, R87.2
unnamed: C88.1, R85.1, R86.2, U43.3
unnamed: OUT-21.1, U44.6
unnamed: C91.1, U46.1
unnamed: C89.1, R91.1, R92.2, U45.4
unnamed: C91.2, R91.2
unnamed: C92.1, R89.1, R90.2, U45.3
unnamed: OUT-22.1, U46.6
unnamed: C95.1, U48.1
unnamed: C93.1, R95.1, R96.2, U47.4
unnamed: C95.2, R95.2
unnamed: C96.1, R93.1, R94.2, U47.3
unnamed: OUT-23.1, U48.6
unnamed: C99.1, U50.1
unnamed: C97.1, R99.1, R100.2, U49.4
unnamed: C99.2, R99.2
unnamed: C100.1, R97.1, R98.2, U49.3
unnamed: OUT-24.1, U50.6
unnamed: C103.1, U52.1
unnamed: C101.1, R103.1, R104.2, U51.4
unnamed: C103.2, R103.2
unnamed: C104.1, R101.1, R102.2, U51.3
unnamed: OUT-25.1, U52.6
unnamed: C107.1, U54.1
unnamed: C105.1, R107.1, R108.2, U53.4
unnamed: C107.2, R107.2
unnamed: C108.1, R105.1, R106.2, U53.3
unnamed: OUT-26.1, U54.6
unnamed: C111.1, U56.1
unnamed: C109.1, R111.1, R112.2, U55.4
unnamed: C111.2, R111.2
unnamed: C112.1, R109.1, R110.2, U55.3
unnamed: OUT-27.1, U56.6
unnamed: C115.1, U58.1
unnamed: C113.1, R115.1, R116.2, U57.4
unnamed: C115.2, R115.2
unnamed: C116.1, R113.1, R114.2, U57.3
unnamed: OUT-28.1, U58.6
unnamed: C119.1, U60.1
unnamed: C117.1, R119.1, R120.2, U59.4
unnamed: C119.2, R119.2
unnamed: C120.1, R117.1, R118.2, U59.3
unnamed: OUT-29.1, U60.6
unnamed: C123.1, U62.1
unnamed: C121.1, R123.1, R124.2, U61.4
unnamed: C123.2, R123.2
unnamed: C124.1, R121.1, R122.2, U61.3
unnamed: OUT-30.1, U62.6
unnamed: C127.1, U64.1
unnamed: C125.1, R127.1, R128.2, U63.4
unnamed: C127.2, R127.2
unnamed: C128.1, R125.1, R126.2, U63.3
unnamed: OUT-31.1, U64.6
unnamed: C131.1, U66.1
unnamed: C129.1, R131.1, R132.2, U65.4
unnamed: C131.2, R131.2
unnamed: C132.1, R129.1, R130.2, U65.3
unnamed: OUT-32.1, U66.6
unnamed: C135.1, U68.1
unnamed: C133.1, R135.1, R136.2, U67.4
unnamed: C135.2, R135.2
unnamed: C136.1, R133.1, R134.2, U67.3
unnamed: OUT-33.1, U68.6
unnamed: C139.1, U70.1
unnamed: C137.1, R139.1, R140.2, U69.4
unnamed: C139.2, R139.2
unnamed: C140.1, R137.1, R138.2, U69.3
unnamed: OUT-34.1, U70.6
unnamed: C143.1, U72.1
unnamed: C141.1, R143.1, R144.2, U71.4
unnamed: C143.2, R143.2
unnamed: C144.1, R141.1, R142.2, U71.3
unnamed: OUT-35.1, U72.6
unnamed: C147.1, U74.1
unnamed: C145.1, R147.1, R148.2, U73.4
unnamed: C147.2, R147.2
unnamed: C148.1, R145.1, R146.2, U73.3
unnamed: OUT-36.1, U74.6
unnamed: C151.1, U76.1
unnamed: C149.1, R151.1, R152.2, U75.4
unnamed: C151.2, R151.2
unnamed: C152.1, R149.1, R150.2, U75.3
unnamed: OUT-37.1, U76.6
unnamed: C155.1, U78.1
unnamed: C153.1, R155.1, R156.2, U77.4
unnamed: C155.2, R155.2
unnamed: C156.1, R153.1, R154.2, U77.3
unnamed: OUT-38.1, U78.6
unnamed: C159.1, U80.1
unnamed: C157.1, R159.1, R160.2, U79.4
unnamed: C159.2, R159.2
unnamed: C160.1, R157.1, R158.2, U79.3
unnamed: OUT-39.1, U80.6
unnamed: C163.1, U82.1
unnamed: C161.1, R163.1, R164.2, U81.4
unnamed: C163.2, R163.2
unnamed: C164.1, R161.1, R162.2, U81.3
unnamed: OUT-40.1, U82.6
unnamed: C167.1, U84.1
unnamed: C165.1, R167.1, R168.2, U83.4
unnamed: C167.2, R167.2
unnamed: C168.1, R165.1, R166.2, U83.3
unnamed: OUT-41.1, U84.6
unnamed: C171.1, U86.1
unnamed: C169.1, R171.1, R172.2, U85.4
unnamed: C171.2, R171.2
unnamed: C172.1, R169.1, R170.2, U85.3
unnamed: OUT-42.1, U86.6
unnamed: C175.1, U88.1
unnamed: C173.1, R175.1, R176.2, U87.4
unnamed: C175.2, R175.2
unnamed: C176.1, R173.1, R174.2, U87.3
unnamed: OUT-43.1, U88.6
unnamed: C179.1, U90.1
unnamed: C177.1, R179.1, R180.2, U89.4
unnamed: C179.2, R179.2
unnamed: C180.1, R177.1, R178.2, U89.3
unnamed: OUT-44.1, U90.6
unnamed: C183.1, U92.1
unnamed: C181.1, R183.1, R184.2, U91.4
unnamed: C183.2, R183.2
unnamed: C184.1, R181.1, R182.2, U91.3
unnamed: OUT-45.1, U92.6
unnamed: C187.1, U94.1
unnamed: C185.1, R187.1, R188.2, U93.4
unnamed: C187.2, R187.2
unnamed: C188.1, R185.1, R186.2, U93.3
unnamed: OUT-46.1, U94.6
unnamed: C191.1, U96.1
unnamed: C189.1, R191.1, R192.2, U95.4
unnamed: C191.2, R191.2
unnamed: C192.1, R189.1, R190.2, U95.3
unnamed: OUT-47.1, U96.6
unnamed: C195.1, U98.1
unnamed: C193.1, R195.1, R196.2, U97.4
unnamed: C195.2, R195.2
unnamed: C196.1, R193.1, R194.2, U97.3
unnamed: OUT-48.1, U98.6
unnamed: C199.1, U100.1
unnamed: C197.1, R199.1, R200.2, U99.4
unnamed: C199.2, R199.2
unnamed: C200.1, R197.1, R198.2, U99.3
unnamed: OUT-49.1, U100.6
unnamed: C203.1, U102.1
unnamed: C201.1, R203.1, R204.2, U101.4
unnamed: C203.2, R203.2
unnamed: C204.1, R201.1, R202.2, U101.3
unnamed: OUT-50.1, U102.6
unnamed: C207.1, U104.1
unnamed: C205.1, R207.1, R208.2, U103.4
unnamed: C207.2, R207.2
unnamed: C208.1, R205.1, R206.2, U103.3
unnamed: OUT-51.1, U104.6
unnamed: C211.1, U106.1
unnamed: C209.1, R211.1, R212.2, U105.4
unnamed: C211.2, R211.2
unnamed: C212.1, R209.1, R210.2, U105.3
unnamed: OUT-52.1, U106.6
unnamed: C215.1, U108.1
unnamed: C213.1, R215.1, R216.2, U107.4
unnamed: C215.2, R215.2
unnamed: C216.1, R213.1, R214.2, U107.3
unnamed: OUT-53.1, U108.6
unnamed: C219.1, U110.1
unnamed: C217.1, R219.1, R220.2, U109.4
unnamed: C219.2, R219.2
unnamed: C220.1, R217.1, R218.2, U109.3
unnamed: OUT-54.1, U110.6
unnamed: C223.1, U112.1
unnamed: C221.1, R223.1, R224.2, U111.4
unnamed: C223.2, R223.2
unnamed: C224.1, R221.1, R222.2, U111.3
unnamed: OUT-55.1, U112.6
unnamed: C227.1, U114.1
unnamed: C225.1, R227.1, R228.2, U113.4
unnamed: C227.2, R227.2
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
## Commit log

2022-02-02 Layout
2022-02-10 Prod_ID for mic
    -also moved Via away from pad 6
    -and routed a tiny airwire on VCC pad
2022-02-11 Added test point for OUT-
2022-02-14 Checklist catches
    -Attribution for original design
    -test point for OUT- moved to 50 though grid
    -nudges some vias to avoid silk
    -adjust value text objects for assembly sheet
2022-02-15 Production panel BRD and Gerbers v10
2022-03-16 Update README.md
    Updating README with current photos and product links.
2022-03-16 Update README
    Updating product name
